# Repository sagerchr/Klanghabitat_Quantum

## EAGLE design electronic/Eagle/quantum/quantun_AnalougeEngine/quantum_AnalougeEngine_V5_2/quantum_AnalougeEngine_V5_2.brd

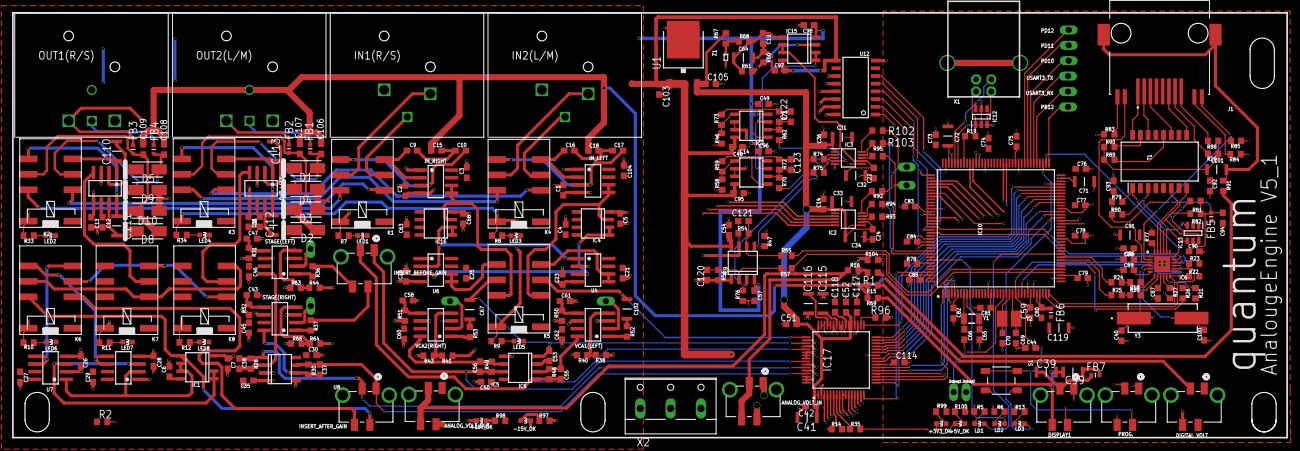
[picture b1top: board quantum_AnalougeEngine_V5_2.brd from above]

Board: 4 copper layers, 210.0 x 70.0 mm, 319 parts (0 on the bottom side), 248 nets.

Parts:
+3V3_OK, +5V_OK, +15V_OK: LED_GREEN_SMD; WL-SMCW_0603
-15V_OK: LED_GREEN_SMD; WL-SMCW_0603
ANALOG_VOLT_IN: 90814-0204; MOLEX_90814-0204
ANALOG_VOLT_OUT: 90814-0204; MOLEX_90814-0204
C1, C2, C3, C4, C5, C6, C7, C8, C11, C12, C13, C14, C19, C20, C21, C22, C23, C24, C25, C26, C27, C28, C29, C30, C35, C36, C42, C43, C44, C45, C46, C47, C48, C49, C50, C51, C52, C53, C54, C57, C58, C59, C60, C61, C62, C63, C68, C73, C74, C75, C76, C77, C78, C79, C80, C81, C82, C83, C84, C85, C86, C87, C90, C92, C93, C94, C95, C96, C97, C98, C104, C105, C106, C107, C108, C109, C114: 100 nF; C0603
C9, C10, C16, C17, C89: 470 pF; C0603
C15, C18: 47 pF; C0603
C31, C32, C33, C34, C39, C41, C64, C67, C91, C99, C102, C110, C111, C112, C113, C115, C116: 10 uF; C1206
C37, C38, C55, C56, C120, C121, C122, C123: 22 pF; C0603
C40, C100: 30 pF; C0603
C65, C66: 2.7 pF; C0603
C69, C70: 4.3 pF; C0603
C71, C72: 2.2 uF; C1206
C88, C117, C118: 1 uF; C0603
C101, C119: 4.7 uF; C1206
C103: 330 nF; C0603
D1, D2, D3, D4, D5, D8, D9, D10: FM4004-W; DIONM5025X231N
DEBUG1, DEBUG2: TPTHT; THT_PIN
DIGITAL_VOLT: 90814-0204; MOLEX_90814-0204
DISPLAY1: 90814-0204; MOLEX_90814-0204
FB1, FB2, FB3, FB4, FB6, FB7: FERITTE-BREAD; BLM18KG102SH1J
FB5: 0 R; BLM18KG102SH1J
IC1, IC4, IC5, IC8, IC16: OP275; SOIC8
IC2, IC3: DAC084S085CIMM_NOPB; SOP50P490X110-10N
IC6: LAN8742A-CZ-TR; QFN50P400X400X100-25N
IC7, IC9, IC14, IC15: NE5532; SOIC8
IC10: STM32F767ZIT6; QFP50P2200X2200X160-144N
IC12: ESDA6V1BC6; SOT95P280X145-6N
IC13: USBLC6-4SC6; SOT95P280X145-6N
IC17: AD7606BSTZ-6; QFP50P1200X1200X160-64N
IN1(R/S), IN2(L/M): NEUTRIK_NC3FAH
INSERT_AFTER_GAIN: 90814-0204; MOLEX_90814-0204
INSERT_BEFORE_GAIN: 90814-0204; MOLEX_90814-0204
IN_LEFT: THAT1240; SO08
IN_RIGHT: THAT1240; SO08
J1: GWLEX-SMT-S988G_Y; GWLEXSMTS988GY
K1, K2, K3, K4, K5, K6, K7, K8: Relay; 351
LD1: LED_YELOW_SMD; WL-SMCW_0603
LD2: LED_RED_SMD; WL-SMCW_0603
LD3: LED_GREEN_SMD; WL-SMCW_0603
LED1, LED2, LED3, LED4, LED5, LED6, LED7, LED8: LED_BLUE_SMD; WL-SMCW_0603
OUT1(R/S), OUT2(L/M): NEUTRIK_NC3MAH
OUT_LEFT: THAT1646; SO08
OUT_RIGHT: THAT1646; SO08
PROG.: 90814-0204; MOLEX_90814-0204
R1, R2, R15, R16, R69, R91, R104: 0 R; R0603
R5, R6, R7, R8, R9, R10, R11, R12, R13, R33, R34, R97, R98: 680 R; R0603
R14, R18, R19, R20, R21, R23, R27, R35, R46, R54, R55, R56, R57, R58, R60, R61, R62, R67, R70, R71, R72, R74, R75, R78, R85, R96: 10 k; R0603
R22: 1k5; R0603
R24, R25, R26: 33 R; R0603
R28, R30, R36, R37, R48, R49, R52, R53, R68: 20 k; R0603
R29, R88, R89, R90: 75 R; R0603
R31, R32, R50, R51: 5k1; R0603
R38, R41, R44, R64: 27 k; R0603
R40, R43, R63, R66: 160 k; R0603
R47, R76: 1k8; R0603
R59, R73: 56 k; R0603
R77: 12k1; R0603
R79, R80, R81, R82: 50 R; R0603
R83, R84: 270 R; R0603
R92, R93, R94, R95, R102, R103: 500 R; R0603
R99: 65 R; R0603
R100: 150 R; R0603
S1: PTS647SN50SMTR2LFS
STAGE(LEFT): THAT2181SO8-US; SO08
STAGE(RIGHT): THAT2181SO8-US; SO08
T1: H1102NL; SOIC127P940X597-16N
TP01, TP02, TP03, TP04, TP05, TP06, TP07, TP08, TP09, TP10, TP36, TP37: TPTHT; THT_PIN
U1: 78*_SMD; TO252
U4, U6, U7, U8: THAT1240; SO08
U12: ULN2003; SOIC16
VCA1(LEFT), VCA2(RIGHT): THAT2181SO8-US; SO08
X1: SMARTPRJ_PN61729
X2: W237-103
Y1: NX3215SA-32.768K-STD-MUA-8; NX3215SA
Y2: NX3225GD-8MHZ-STD-CRA-3; RESC3226X100N
Y3: ABLS2-25.000MHZ-D4YF-T; ABLS
Z1: ZENER_DIODE_BZT; SODFL1608X65N

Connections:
0,5V_DAC: IC7.3, IC14.3, IC15.1, IC15.2
1V_DAC: C22.1, C32.1, IC3.7, IC15.6, IC15.7
1V_DAC_UNBUFFERD: C19.1, C64.1, IC15.5, R61.2, R68.1
2V_DAC_REF: R67.1, R68.2, Z1.1
8MHZ_CRYSTAL_A: C70.1, IC10.23, Y2.1
8MHZ_CRYSTAL_B: C69.1, IC10.24, Y2.2
32.768KHZ_A: C66.1, IC10.8, Y1.1
32.768KHZ_B: C65.1, IC10.9, Y1.2
+3V3: C59.2, C73.1, C74.1, C75.1, C76.1, C77.1, C78.1, C79.1, C81.2, C82.2, C83.1, C84.1, C85.1, C86.2, C87.2, C90.2, C91.1, C92.2, C93.2, C119.2, DIGITAL_VOLT.1, FB5.1, FB6.1, IC6.1, IC6.9, IC6.19, IC10.6, IC10.17, IC10.30, IC10.39, IC10.52, IC10.62, IC10.72, IC10.84, IC10.95, IC10.108, IC10.121, IC10.131, IC10.143, IC10.144, R18.1, R20.1, R21.1, R22.1, R23.2, R99.2, T1.2, T1.7
+5V: C99.1, C114.1, DIGITAL_VOLT.4, FB7.2, IC17.23, R35.2, R96.1, R100.2
+5V(ANALOG): C14.1, C24.1, C31.1, C33.1, C34.1, C36.1, C41.1, C42.1, C51.1, C52.1, C105.1, IC2.1, IC2.7, IC3.1, IC17.1, IC17.37, IC17.38, IC17.48, R67.2, U1.3
.: C123.2, IC14.1, R59.2, R72.2
...: C122.2, IC7.1, R71.2, R73.2
AGND: +3V3_OK.1, +5V_OK.1, +15V_OK.1, -15V_OK.2, C1.2, C2.2, C3.2, C4.2, C5.2, C6.2, C7.2, C8.2, C11.2, C12.2, C13.2, C14.2, C19.2, C20.2, C21.2, C22.2, C23.2, C24.2, C25.2, C26.2, C27.2, C28.2, C29.2, C30.2, C31.2, C32.2, C33.2, C34.2, C35.2, C36.2, C40.1, C41.2, C42.2, C43.2, C44.1, C45.2, C46.2, C47.2, C48.2, C49.2, C50.2, C51.2, C52.2, C53.2, C54.2, C57.2, C58.2, C59.1, C60.2, C61.2, C62.2, C63.2, C64.2, C65.2, C66.2, C68.2, C69.2, C70.2, C71.2, C72.2, C73.2, C74.2, C75.2, C76.2, C77.2, C78.2, C79.2, C80.1, C81.1, C82.1, C83.2, C84.2, C85.2, C86.1, C87.1, C88.1, C89.1, C90.1, C91.2, C92.1, C93.1, C94.1, C95.2, C96.2, C97.2, C98.2, C100.1, C103.2, C104.2, C105.2, C114.2, C115.2, C116.2, C117.2, C118.2, C119.1, IC2.6, IC3.6, IC5.3, IC5.5, IC6.25, IC8.3, IC8.5, IC10.16, IC10.31, IC10.38, IC10.51, IC10.61, IC10.83, IC10.94, IC10.107, IC10.120, IC10.130, IC12.2, IC12.5, IC13.2, IC17.2, IC17.26, IC17.35, IC17.40, IC17.41, IC17.43, IC17.46, IC17.47, IC17.50, IC17.52, IC17.54, IC17.55, IC17.56, IC17.58, IC17.60, IC17.62, IC17.63, IC17.64, IN_LEFT.1, IN_RIGHT.1, OUT_LEFT.3, OUT_RIGHT.3, PROG..4, R1.2, R5.1, R6.1, R13.1, R14.2, R15.2, R16.2, R27.1, R46.1, R47.1, R58.1, R60.1, R69.2, R76.1, R77.2, R78.2, R83.1, R84.1, R85.1, R104.2, S1.1, S1.2, STAGE(LEFT).3, STAGE(LEFT).6, STAGE(RIGHT).3, STAGE(RIGHT).6, U1.2, U4.2, U6.1, U7.2, U8.1, VCA1(LEFT).3, VCA1(LEFT).6, VCA2(RIGHT).3, VCA2(RIGHT).6, X1.4, X2.3, Z1.2
A_GND_TO_STAR: ANALOG_VOLT_IN.3, ANALOG_VOLT_IN.4, ANALOG_VOLT_OUT.3, ANALOG_VOLT_OUT.4, R16.1
BOOT0: IC10.138, R78.1
BUSY: IC10.88, IC17.14
CHASIS: X1.P$1, X1.P$2
CHASSIS: C15.1, C18.1, C106.2, C107.2, C108.2, C109.2, IN1(R/S).1, IN2(L/M).1, OUT1(R/S).1, OUT1(R/S).G, OUT2(L/M).1, OUT2(L/M).G, R1.1, R2.1, R91.1, X2.1
CS: IC10.123, IC17.13
CS_DAC1: IC10.134, R94.2
CS_DAC2: IC10.135, R95.2
CV_A_B: IC10.113, IC17.9, IC17.10
DAC2_OUT1(OFFSET_VCA1): IC9.3, R74.2, R76.2
DAC2_OUT2(OFFSET_VCA2): IC9.5, R47.2, R75.2
DAC2_OUT3: IC3.4, R62.1
DAC2_OUT4: IC3.5, R70.1
DAC_OUT1: IC10.40, R57.1
DAC_OUT2: IC10.41, R55.1
DB0: IC10.141, IC17.16
DB1: IC10.142, IC17.17
DB2: IC10.1, IC17.18
DB3: IC10.2, IC17.19
DB4: IC10.3, IC17.20
DB5: IC10.4, IC17.21
DB6: IC10.5, IC17.22
DB7: IC10.58, IC17.24
DB8: IC10.59, IC17.25
DB9: IC10.60, IC17.27
DB10: IC10.63, IC17.28
DB11: IC10.64, IC17.29
DB12: IC10.65, IC17.30
DB13: IC10.66, IC17.31
DB14: IC10.67, IC17.32
DB15: IC10.68, IC17.33
DEBUG1: DEBUG1.P$1, IC10.21
DEBUG2: DEBUG2.P$1, IC10.115
DIN_DAC: IC10.29, R93.2, R103.2, TP04.P$1
DISPLAY_GND_TO_STAR: C39.2, C99.2, DISPLAY1.4, R69.1
D_GND_TO_STAR: DIGITAL_VOLT.3, R15.1
E+_OUT_STAGE_LEFT: IC7.6, IC7.7, STAGE(LEFT).2, TP02.P$1
E+_OUT_STAGE_RIGHT: IC14.6, IC14.7, STAGE(RIGHT).2, TP01.P$1
EC+_VCA1(LFT): C120.2, IC9.1, R56.2, TP37.P$1, VCA1(LEFT).2
EC+_VCA2(RIGHT): C121.2, IC9.7, R54.2, TP36.P$1, VCA2(RIGHT).2
ETHERNET_CHASSIS: C101.2, J1.MP1, J1.MP2, R91.2
FRST: IC10.122, IC17.15
L: IC4.3, IN_LEFT.5, IN_LEFT.6, K5.Q1
L/M_IN(VCA1_IN): C102.1, IC17.49, K5.P1
L/M_OUT(OUT_STAGE_LEFT): IC1.3, INSERT_AFTER_GAIN.4, K6.Q1
L/M_OUT(OUT_STAGE_LEFT)_BEFORE: C38.2, IC5.1, IC17.59, INSERT_AFTER_GAIN.3, R28.2
L/M_OUT(VCA1_OUT): C55.2, IC8.1, IC17.53, INSERT_BEFORE_GAIN.3, R48.2
L/M_OUT+: C112.2, K3.S2, OUT_LEFT.8
L/M_OUT-: C113.2, K3.S1, OUT_LEFT.1
LD1: IC10.46, LD1.2
LD2: IC10.137, LD2.2
LD3: IC10.75, LD3.2
LED1: IC6.3, J1.10
LED2: IC6.2, J1.12, R85.2
M: K5.S1, U4.5, U4.6
M1: K6.S1, U7.5, U7.6
unnamed: C9.1, IN_RIGHT.2, K1.S1
unnamed: C10.2, IN_RIGHT.3, K1.S2
unnamed: C9.2, C10.1, C15.2
unnamed: IC17.34, R96.2
unnamed: K6.P1, K7.S1, K8.Q1
unnamed: LD1.1, R5.2
unnamed: C17.2, IN_LEFT.3, K4.S2
unnamed: K1.Q1, K2.Q1
unnamed: C16.2, C17.1, C18.2
unnamed: IC10.101, R19.1
unnamed: K1.Q2, K2.Q2
unnamed: LD2.1, R6.2
unnamed: C16.1, IN_LEFT.2, K4.S1
unnamed: LED1.1, R7.2
unnamed: C71.1, IC10.71
unnamed: LED3.1, R8.2
unnamed: C72.1, IC10.106
unnamed: IC4.1, IC4.2, U4.3, U6.3
unnamed: K6.P2, K7.Q1, K8.S1
unnamed: IC3.10, R102.1
unnamed: IC6.7, R18.2, R24.2
unnamed: IC6.8, R20.2, R25.2
unnamed: IC6.11, R21.2, R26.2
unnamed: IC6.10, R27.2
unnamed: IC6.24, R77.1
unnamed: LED8.1, R12.2
unnamed: C88.2, C89.2, IC6.6
unnamed: K3.Q1, K4.Q1
unnamed: LED7.1, R11.2
unnamed: LED6.1, R10.2
unnamed: K3.Q2, K4.Q2
unnamed: LED5.1, R9.2
unnamed: IC16.1, IC16.2, U4.1, U6.2
unnamed: LD3.1, R13.2
unnamed: J1.1, T1.16
unnamed: J1.2, T1.14
unnamed: J1.3, T1.11
unnamed: IC17.6, R14.1
unnamed: IC3.8, R103.1
unnamed: IC17.7, R35.1
unnamed: C94.2, FB5.2, IC13.5, R79.2, R80.2, R81.2, R82.2
unnamed: FB1.2, OUT2(L/M).3
unnamed: IC1.6, IC1.7, U7.1, U8.2
unnamed: FB4.2, OUT1(R/S).3
unnamed: IC1.1, IC1.2, U7.3, U8.3
unnamed: J1.6, T1.9
unnamed: C107.1, D2.2, D3.1, FB2.1, K3.P2
unnamed: C38.1, IC5.2, R28.1, STAGE(LEFT).8
unnamed: LED2.1, R33.2
unnamed: J1.11, R84.2
unnamed: LED4.1, R34.2
unnamed: J1.9, R83.2
unnamed: C37.1, IC5.6, R30.1, STAGE(RIGHT).8
unnamed: C43.1, R32.2, STAGE(RIGHT).5
unnamed: R36.2, STAGE(LEFT).1
unnamed: IC2.2, R38.2
unnamed: IC2.3, R41.2
unnamed: IC2.4, R44.2
unnamed: IC2.5, R64.2
unnamed: IC3.2, R74.1
unnamed: IC3.3, R75.1
unnamed: IC7.5, R46.2, R73.1
unnamed: C120.1, IC9.2, R56.1, R57.2
unnamed: C55.1, IC8.2, R48.1, VCA1(LEFT).8
unnamed: R52.2, VCA1(LEFT).1
unnamed: IC14.5, R58.2, R59.1
unnamed: IC15.3, R60.2, R61.1
unnamed: R37.2, STAGE(RIGHT).1
unnamed: C40.2, IC6.4, Y3.1
unnamed: C100.2, IC6.5, Y3.2
unnamed: C102.2, R52.1
unnamed: C122.1, IC7.2, R62.2, R71.1
unnamed: C47.1, R31.2, STAGE(LEFT).5
unnamed: C123.1, IC14.2, R70.2, R72.1
unnamed: C56.1, IC8.6, R49.1, VCA2(RIGHT).8
unnamed: -15V_OK.1, R97.2
unnamed: C58.1, R51.2, VCA2(RIGHT).5
unnamed: C67.2, R53.1
unnamed: R53.2, VCA2(RIGHT).1
unnamed: C61.1, R50.2, VCA1(LEFT).5
unnamed: C121.1, IC9.6, R54.1, R55.2
unnamed: +15V_OK.2, R98.1
unnamed: +3V3_OK.2, R99.1
unnamed: +5V_OK.2, R100.1
unnamed: C109.1, D8.2, D10.1, FB3.1, K2.P2
unnamed: J1.7, R29.2
unnamed: J1.8, R88.2
unnamed: R89.2, T1.12
unnamed: R90.2, T1.15
unnamed: C101.1, R29.1, R88.1, R89.1, R90.1
unnamed: IC2.10, R92.1
unnamed: C39.1, DISPLAY1.3, FB7.1
unnamed: IC2.8, R93.1
unnamed: IC2.9, R94.1
unnamed: IC3.9, R95.1
unnamed: INSERT_BEFORE_GAIN.2, R37.1
unnamed: INSERT_BEFORE_GAIN.4, R36.1
unnamed: C111.1, OUT_RIGHT.7
unnamed: C110.1, OUT_RIGHT.2
unnamed: C113.1, OUT_LEFT.2
unnamed: C112.1, OUT_LEFT.7
unnamed: C115.1, IC17.42
unnamed: C116.1, IC17.44, IC17.45
unnamed: C117.1, IC17.36
unnamed: C118.1, IC17.39
unnamed: C80.2, FB6.2, IC10.32, IC10.33
NEGATIVE_IN(L/M): IN2(L/M).3, K4.P1
NEGATIVE_IN(R/S): IN1(R/S).3, K1.P1
NEGATIVE_OUT(L/M): C106.1, D1.2, D4.1, FB1.1, K3.P1
NGATIVE_OUT(R/S): C108.1, D5.2, D9.1, FB4.1, K2.P1
NRST: C44.2, IC6.15, IC10.25, PROG..2, S1.3, S1.4
OS0: IC10.98, IC17.3
OS1: IC10.99, IC17.4
OS2: IC10.111, IC17.5
OUT1_DRIVER: K1.2, K2.2, R7.1, R33.1, U12.16
OUT2_DRIVER: K3.2, K4.2, R8.1, R34.1, U12.15
OUT3_DRIVER: K5.2, R9.1, U12.14
OUT4_DRIVER: K6.2, R10.1, U12.13
OUT5_DRIVER: K7.2, R11.1, U12.12
OUT6_DRIVER: K8.2, R12.1, U12.11
OUT_L/M: K8.P1, OUT_LEFT.4
OUT_R/S: K7.P1, OUT_RIGHT.4
PB12: IC10.73, TP05.P$1
PD10: IC10.79, TP08.P$1
PD11: IC10.80, TP09.P$1
PD12: IC10.81, TP10.P$1
POSITIVE_IN(L/M): IN2(L/M).2, K4.P2
POSITIVE_IN(R/S): IN1(R/S).2, K1.P2
POSITIVE_OUT(L/M): FB2.2, OUT2(L/M).2
POSITIVE_OUT(R/S): FB3.2, OUT1(R/S).2
R: IC16.3, IN_RIGHT.5, IN_RIGHT.6, K5.Q2
R/S_IN(VCA2_IN): C67.1, IC17.51, K5.P2
R/S_OUT(OUT_STAGE_RIGHT): IC1.5, INSERT_AFTER_GAIN.2, K6.Q2
R/S_OUT(OUT_STAGE_RIGHT)_BEFORE: C37.2, IC5.7, IC17.61, INSERT_AFTER_GAIN.1, R30.2
R/S_OUT(VCA2_OUT): C56.2, IC8.7, IC17.57, INSERT_BEFORE_GAIN.1, R49.2
R/S_OUT+: C111.2, K2.S2, OUT_RIGHT.8
R/S_OUT-: C110.2, K2.S1, OUT_RIGHT.1
RANGE: IC10.112, IC17.8
RD: IC10.116, IC17.12
RD_N: IC6.22, IC13.6, R82.1, T1.8
RD_P: IC6.23, IC13.1, R81.1, T1.6
RELAIS1: IC10.57, U12.1
RELAIS2: IC10.56, U12.2
RELAIS3: IC10.132, U12.3
RELAIS4: IC10.125, U12.4
RELAIS5: IC10.127, U12.5
RELAIS6: IC10.124, U12.6
RELAIS_TO_STAR_GND: R104.1, U12.8
RESET: IC10.87, IC17.11
RMII_CRS_DV: IC10.43, R26.1
RMII_MDC: IC6.13, IC10.27
RMII_MDIO: IC6.12, IC10.36, R22.2
RMII_REF_CLK: IC6.14, IC10.35, R23.1
RMII_RXD0: IC10.44, R25.1
RMII_RXD1: IC10.45, R24.1
RMII_TXD0: IC6.17, IC10.128
RMII_TXD1: IC6.18, IC10.74
RMII_TX_EN: IC6.16, IC10.126
S: K5.S2, U6.5, U6.6
S1: K6.S2, U8.5, U8.6
SCLK_DAC: IC10.69, R92.2, R102.2, TP03.P$1
SWCLK: IC10.109, PROG..1
SWDIO: IC10.105, PROG..3
SYM1: R38.1, R40.2, VCA1(LEFT).4
SYM2: R41.1, R43.2, VCA2(RIGHT).4
SYM3: R44.1, R63.2, STAGE(LEFT).4
SYM4: R64.1, R66.2, STAGE(RIGHT).4
TD_N: IC6.20, IC13.4, R80.1, T1.3
TD_P: IC6.21, IC13.3, R79.1, T1.1
USART3_RX: IC10.77, TP06.P$1
USART3_TX: IC10.78, TP07.P$1
USART6_RX: DISPLAY1.2, IC10.97
USART6_TX: DISPLAY1.1, IC10.96
USB_N: IC10.103, IC12.3, X1.2
USB_P: IC10.104, IC12.6, X1.3
USB_VBUS: IC12.1, R19.2, X1.1
V+: ANALOG_VOLT_IN.1, ANALOG_VOLT_OUT.1, C3.1, C4.1, C6.1, C8.1, C12.1, C21.1, C25.1, C27.1, C29.1, C30.1, C45.1, C46.1, C48.1, C50.1, C54.1, C60.1, C62.1, C63.1, C95.1, C97.1, C103.1, C104.1, D1.1, D2.1, D5.1, D8.1, IC1.8, IC4.8, IC5.8, IC7.8, IC8.8, IC9.8, IC14.8, IC15.8, IC16.8, IN_LEFT.7, IN_RIGHT.7, K1.1, K2.1, K3.1, K4.1, K5.1, K6.1, K7.1, K8.1, LED1.2, LED2.2, LED3.2, LED4.2, LED5.2, LED6.2, LED7.2, LED8.2, OUT_LEFT.6, OUT_RIGHT.6, R98.2, STAGE(LEFT).7, STAGE(RIGHT).7, U1.1, U4.7, U6.7, U7.7, U8.7, U12.9, VCA1(LEFT).7, VCA2(RIGHT).7
V-: ANALOG_VOLT_IN.2, ANALOG_VOLT_OUT.2, C1.1, C2.1, C5.1, C7.1, C11.1, C13.1, C20.1, C23.1, C26.1, C28.1, C35.1, C49.1, C53.1, C57.1, C68.1, C96.1, C98.1, D3.2, D4.2, D9.2, D10.2, IC1.4, IC4.4, IC5.4, IC7.4, IC8.4, IC9.4, IC14.4, IC15.4, IC16.4, IN_LEFT.4, IN_RIGHT.4, OUT_LEFT.5, OUT_RIGHT.5, R31.1, R32.1, R40.1, R43.1, R50.1, R51.1, R63.1, R66.1, R97.1, U4.4, U6.4, U7.4, U8.4
